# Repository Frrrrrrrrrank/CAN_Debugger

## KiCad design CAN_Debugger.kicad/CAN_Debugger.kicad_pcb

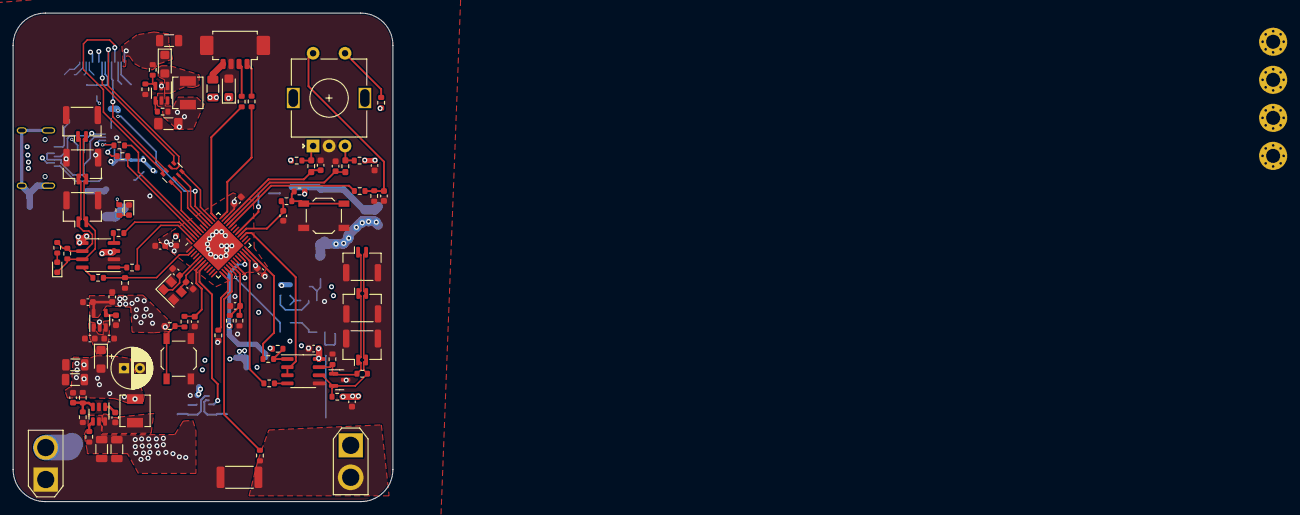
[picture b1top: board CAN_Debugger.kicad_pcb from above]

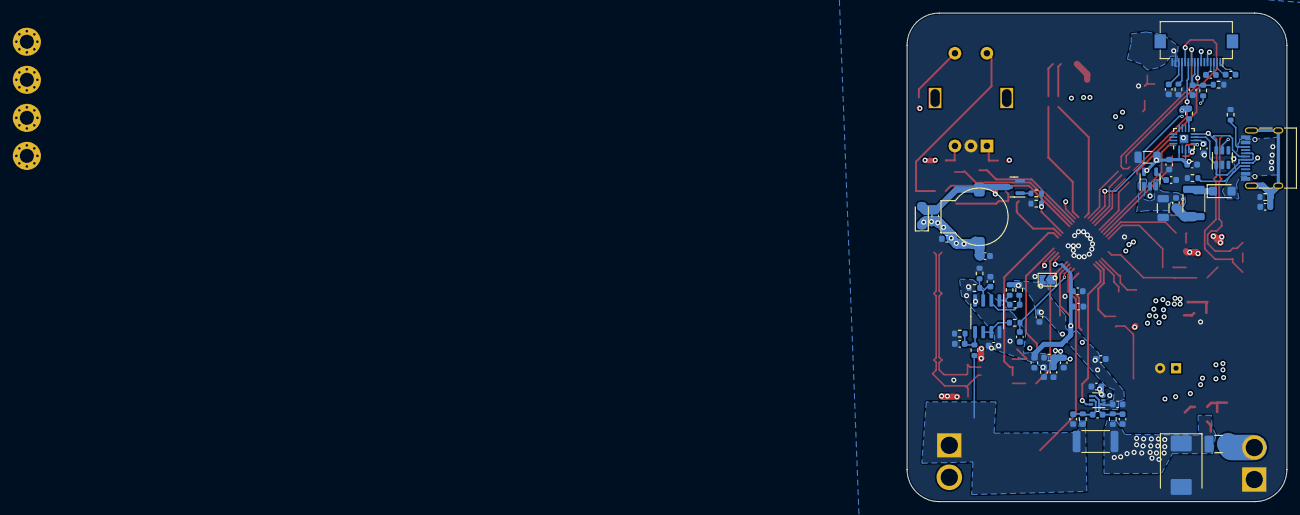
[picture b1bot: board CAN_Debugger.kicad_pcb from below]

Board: 4 copper layers, 59.4 x 76.4 mm, 169 parts (68 on the bottom side), 102 nets.

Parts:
BZ1: Buzzer; MLT-9032
C1, C2, C6, C7, C37, C45: 10uF; C_1206_3216Metric
C3: 47uF; CP_Radial_D6.3mm_P2.50mm
C4, C9, C12, C25, C26, C27, C28, C30, C31, C33, C34, C35, C38, C39, C40, C41, C42, C46, C49, C50, C57, C58, C59, C70, C76, C88, C104, C105: 100n; C_0603_1608Metric
C5, C8, C14, C23: 20p; C_0603_1608Metric
C10, C13, C22, C24, C29, C80: 10u; C_0603_1608Metric
C11: 10n; C_0603_1608Metric
C15, C16: 1uf; C_0603_1608Metric
C17: 2.2uf; C_0603_1608Metric
C20, C21, C36: 100nF; C_0603_1608Metric
C32, C47, C52, C53, C54: C; C_0603_1608Metric
C43, C44: 10nF; C_0603_1608Metric
C48: 22u; C_1206_3216Metric
C51: 22u; C_1206_3216Metric_Pad1.33x1.80mm_HandSolder
D1: SMCJ28A; D_SMC
D3, D5, D6, D10: D_Schottky; D_SMF
D4, D9: LED; LED_0603_1608Metric
D7: SMF3.3A; D_SMF
D8: SM712; SOT-23
F1: Fuse; Fuse_1210_3225Metric_Pad1.42x2.65mm_HandSolder
F2: Polyfuse; Fuse_1206_3216Metric
F4: Fuse; Fuse_1812_4532Metric
FB1: 120R@100MHz; L_0603_1608Metric
H1, H2, H3, H4: MountingHole_Pad; MountingHole_2.2mm_M2_Pad_Via
J1: Conn_01x02; AMASS_XT30U-M_1x02_P5.0mm_Vertical
J2: Conn_01x04_MountingPin; Molex_PicoBlade_53261-0471_1x04-1MP_P1.25mm_Horizontal
J3: Conn_01x02; AMASS_XT30U-F_1x02_P5.0mm_Vertical
J4: Conn_01x16_Socket; Hirose_FH12-16S-0.5SH_1x16-1MP_P0.50mm_Horizontal
J5: USB_C_Receptacle_USB2.0; USB_C_Receptacle_HRO_TYPE-C-31-M-12
J6: RS-485; JST_GH_BM02B-GHS-TBT_1x02-1MP_P1.25mm_Vertical
J7, J8, J9: CAN; JST_GH_BM02B-GHS-TBT_1x02-1MP_P1.25mm_Vertical
J15, J16: RS-485; JST_GH_SM02B-GHS-TB_1x02-1MP_P1.25mm_Horizontal
JP1: SolderJumper_2_Open; SolderJumper-2_P1.3mm_Open_TrianglePad1.0x1.5mm
L1: L; L_Sunlord_MWSA0402S
L2: 4.7u; L_Sunlord_MWSA0402S
L3: L_Ferrite; L_0603_1608Metric
Q1: AO3400A; SOT-23
R1, R3, R10, R19, R23, R28, R38, R39, R40, R42, R50: 10k; R_0603_1608Metric
R2: 53.6k; R_0603_1608Metric
R4, R44: R; R_2512_6332Metric
R5: 330R; R_0603_1608Metric
R6, R31: 10k; R_0603_1608Metric_Pad0.98x0.95mm_HandSolder
R7, R8, R11, R20, R63: 33r; R_0603_1608Metric
R9, R12, R13, R57: 120r; R_0603_1608Metric
R14, R15, R45, R51: R; R_0603_1608Metric
R16, R17, R21: 100k 25ppm; R_0603_1608Metric
R18, R22, R27: 330; R_0603_1608Metric
R24, R62: 1k; R_0603_1608Metric
R25: 10k 25ppm; R_0603_1608Metric
R29: 120R; R_0603_1608Metric
R30, R36: 10K; R_0603_1608Metric
R32, R33: 33R; R_0603_1608Metric
R34, R35: 5.1k; R_0603_1608Metric
R37: 1M; R_0603_1608Metric
R41, R48, R52: 100k; R_0603_1608Metric
R53, R56, R58: 4.7k; R_0603_1608Metric
R54, R55: 100; R_0603_1608Metric
R59, R60: 100r 25ppm; R_0603_1608Metric
R61: 19k; R_0603_1608Metric
RN1: R_Pack04; R_Array_Convex_4x0603
SW1, SW3: SW_Push; SW_SPST_TL3342
SW4: RotaryEncoder_Switch; RotaryEncoder_Alps_EC11E-Switch_Vertical_H20mm
U1: SN75176AD; SOIC-8_3.9x4.9mm_P1.27mm
U2: RY8411; SOT-23-6
U3, U10: RS3236; SOT-23-5
U5: SIT1042T/3; SOIC-8_3.9x4.9mm_P1.27mm
U6: IP4220CZ6; SOT-23-6
U7: INA186; SOT-363_SC-70-6
U8: STM32G431CBUx; QFN-48-1EP_7x7mm_P0.5mm_EP5.6x5.6mm
U9: CH343P; TQFN-16-1EP_3x3mm_P0.5mm_EP1.23x1.23mm
U13: MT3608; SOT-23-6
U14: GS8332-SR; SOIC-8_3.9x4.9mm_P1.27mm
Y1: 25MHz; Crystal_SMD_3225-4Pin_3.2x2.5mm

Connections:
24v_motor: J3.1, R4.2, R21.2, R60.1
+3.3V: C12.1, C13.1, C25.1, C26.1, C27.1, C28.1, C32.1, C41.1, C42.1, C52.1, D7.1 (A1), F2.1, J4.7, L3.1, R19.1, R23.1, R38.1, R39.2, R40.1, R53.1, U3.5 (OUT), U5.5 (VIO), U7.3 (V+), U8.1 (VBAT), U8.23 (VDD), U8.35 (VDD), U8.48 (VDD)
+3.3VA: C29.1, C30.1, C53.1, C54.1, C70.1, L3.2, R16.2, R48.1, U8.21 (VDDA), U14.8 (VDD)
+3.3V_USBTTL: C20.1, C21.1, C36.1, C45.1, U9.1 (VIO), U9.3 (VDD5), U9.6 (V3), U10.5 (OUT)
+5V: BZ1.2 (+), C1.1, C2.1, C3.1, C5.1, C22.2, C23.2, C24.2, C49.1, C50.1, C51.1, D3.2 (A), D5.1 (K), J4.5, L1.2, L2.1, R2.1, R50.1, R58.2, U1.8 (VCC), U5.3 (VCC), U13.5 (IN)
+24V: C6.1, C7.1, D1.1 (K), F1.1, R1.1, R4.1, R59.1, U2.5 (IN)
/1.65Vref: C40.1, C76.1, C80.1, JP1.2 (B), R20.1, R24.1, U7.1 (REF)
/VBUS_CONNECTOR: D6.2 (A), J5.A4 (VBUS), J5.A9 (VBUS), J5.B4 (VBUS), J5.B9 (VBUS)
A+: D8.2 (A2), J6.2, J15.2, J16.2, R57.2, R58.1, U1.6 (A)
A_I: U7.6, U8.8 (PA0)
B-: D8.1 (A1), J6.1, J15.1, J16.1, R56.2, R57.1, U1.7 (B)
BUZZER: R10.2, R11.1, U8.29 (PC6)
C1N: C16.2, J4.4
C1P: C16.1, J4.3
C2N: C15.2, J4.2
C2P: C15.1, J4.1
CANH: D9.1 (K), J7.2, J8.2, J9.2, R9.2, U5.7 (CANH)
CANL: J7.1, J8.1, J9.1, R9.1, R15.1, U5.6 (CANL)
CAN_RX: R8.1, U8.46 (PB8)
CAN_STB: R29.1, R30.1, U8.2 (PC13)
CAN_TX: R7.1, U8.47 (PB9)
CS: J4.8, RN1.5 (R4.2)
D/C: J4.10, RN1.6 (R3.2)
Encoder_button: R42.1, U8.32 (PA10)
GND: C1.2, C2.2, C3.2, C6.2, C7.2, C8.2, C9.2, C10.2, C11.2, C12.2, C13.2, C14.2, C17.2, C20.2, C21.2, C22.1, C24.1, C25.2, C26.2, C27.2, C28.2, C29.2, C30.2, C31.1, C32.2, C33.1, C35.1, C36.2, C37.2, C38.1, C39.2, C40.2, C41.2, C42.2, C43.1, C44.2, C45.2, C46.2, C47.2, C48.2, C49.2, C50.2, C51.2, C52.2, C53.2, C54.2, C57.2, C59.2, C70.2, C76.2, C80.2, C88.1, C104.1, C105.2, D1.2 (A), D4.1 (K), D7.2 (A2), D8.3 (common), J1.1, J2.3, J2.MP (MountPin), J4.16, J5.A1 (GND), J5.A12 (GND), J5.B1 (GND), J5.B12 (GND), J6.MP (MountPin), J7.MP (MountPin), J8.MP (MountPin), J9.MP (MountPin), J15.MP (MountPin), J16.MP (MountPin), Q1.2 (S), R3.2, R10.1, R14.2, R17.1, R25.1, R28.2, R30.2, R34.1, R35.1, R37.1, R41.2, R44.1, R51.2, R52.2, R56.1, R62.2, SW1.2, SW3.2, SW4.C, U1.5 (GND), U2.2 (GND), U3.2 (GND), U5.2 (GND), U6.2 (VN), U7.2 (GND), U8.49 (VSS), U9.2 (GND), U9.17 (GND), U10.2 (GND), U13.2 (GND), U14.4 (VSS), Y1.2, Y1.4
IREF: J4.13, R14.1
NRST: C31.2, R18.2, U8.7 (PG10)
unnamed: BZ1.1 (-), C23.1, D5.2 (A), Q1.3 (D)
unnamed: C46.1, R41.1, R42.2, SW4.S2
unnamed: C57.1, R16.1, R17.2, U14.3 (+)
unnamed: C58.2, R24.2, U14.2 (-)
unnamed: C59.1, R21.1, R25.2, U14.5 (+)
unnamed: C9.1, C10.1, D3.1 (K), U3.1 (IN), U3.3 (EN)
unnamed: D4.2 (A), R36.2
unnamed: D6.1 (K), F4.2
unnamed: D9.2 (A), R15.2
unnamed: D10.2 (A), L2.2, U13.1 (SW)
unnamed: F4.1, FB1.2
unnamed: F1.2, J1.2
unnamed: J2.1, R13.2
unnamed: J2.2, R12.2
unnamed: F2.2, J2.4
unnamed: J5.A5 (CC1), R34.2
unnamed: J5.B5 (CC2), R35.2
unnamed: C43.2, J5.S1 (SHIELD), R37.2
unnamed: Q1.1 (G), R11.2
unnamed: R18.1, R19.2, SW1.1
unnamed: R22.1, R23.2, SW3.1
unnamed: R31.2, R38.2, SW4.B
unnamed: R6.2, R39.1, SW4.A
unnamed: R40.2, SW4.S1
unnamed: R54.1, U1.4 (D)
unnamed: R53.2, R55.2, U1.1 (R)
unnamed: C4.1, U2.1 (BS)
unnamed: R1.2, U2.4 (EN)
unnamed: C5.2, R2.2, R3.1, U2.3 (FB)
unnamed: C4.2, L1.1, U2.6 (LX)
unnamed: C11.1, U3.4 (BP/FB)
unnamed: R8.2, U5.4 (RXD)
unnamed: R29.2, U5.8 (STB)
unnamed: R7.2, U5.1 (TXD)
unnamed: C34.1, C104.2, R59.2, U7.4 (+)
unnamed: C34.2, C105.1, R60.2, U7.5 (-)
unnamed: R32.2, U9.5 (RXD)
unnamed: R33.1, U9.4 (TXD)
unnamed: R5.1, U9.9 (VBUS)
unnamed: C44.1, U10.4 (BP)
unnamed: R50.2, U13.4 (EN)
unnamed: R61.2, R62.1, U13.3 (FB)
unnamed: C58.1, R20.2, U14.1 (OUTA)
unnamed: R63.1, U14.6 (-), U14.7 (OUTB)
PA5: R51.1, U8.13 (PA5)
PA7: R45.1, U8.15 (PA7)
PA11: C39.1, R31.1, U8.33 (PA11)
PA12: C38.2, R6.1, U8.34 (PA12)
PA15: RN1.4 (R4.1), U8.38 (PA15)
PB0: C47.1, R48.2, R52.1, U8.17 (PB0)
PB1: JP1.1 (A), U8.18 (PB1)
PB6: R32.1, U8.44 (PB6)
PB7: R33.2, U8.45 (PB7)
PB10: R54.2, U8.22 (PB10)
PB11: R55.1, U8.24 (PB11)
PB14: U1.2 (~RE), U1.3 (DE), U8.27 (PB14)
PB15: C33.2, R22.2, U8.28 (PB15)
PC4: C88.2, R63.2, U8.16 (PC4)
PC10: R27.1, U8.39 (PC10)
PC11: RN1.3 (R3.1), U8.40 (PC11)
RCC_OSC_IN: C14.1, U8.5 (PF0), Y1.1
RCC_OSC_OUT: C8.1, U8.6 (PF1), Y1.3
RES: C35.2, J4.9, R27.2, R28.1
SCLK: J4.11, RN1.7 (R2.2)
SDIN: J4.12, RN1.8 (R1.2)
SPI1_MOSI: RN1.1 (R1.1), U8.43 (PB5)
SPI1_SCK: RN1.2 (R2.1), U8.41 (PB3)
SYS_JTCK-SWDCLK: R12.1, U8.37 (PA14)
SYS_JTMS-SWDIO: R13.1, U8.36 (PA13)
USB_UART_DM: J5.A7 (D-), J5.B7 (D-), U6.6 (IO4), U9.8 (VD-)
USB_UART_DP: J5.A6 (D+), J5.B6 (D+), U6.1 (IO1), U9.7 (VD+)
VBUS_USBTTL: C37.1, FB1.1, R5.2, R36.1, U6.5 (VP), U10.1 (IN), U10.3 (EN)
VCC: C48.1, D10.1 (K), J4.15, R61.1
VCOMH: C17.1, J4.14
iA+: J3.2, R44.2, R45.2

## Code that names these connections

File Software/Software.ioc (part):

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Mcu.Name=STM32G431C(6-8-B)Ux
Mcu.Package=UFQFPN48
Mcu.UserName=STM32G431CBUx
PA0.GPIOParameters=GPIO_Label
PA0.GPIO_Label=I_AMPLIFIED_SENSE
PA0.Mode=IN1-Single-Ended
PA0.Signal=ADC2_IN1
PA10.Signal=GPIO_Input
PA11.Signal=S_TIM4_CH1
PA12.Signal=S_TIM4_CH2
PA13.Mode=Serial_Wire
PA13.Signal=SYS_JTMS-SWDIO
PA14.Mode=Serial_Wire
PA14.Signal=SYS_JTCK-SWCLK
PA15.Mode=NSS_Signal_Hard_Output
PA15.Signal=SPI1_NSS
PA5.Mode=PGA Internally connected_IO0_BIAS
PA5.Signal=OPAMP2_VINM0
PA7.Mode=PGA Internally connected_IO0_BIAS
PA7.Signal=OPAMP2_VINP
PB10.Mode=Asynchronous
PB10.Signal=USART3_TX
PB11.Mode=Asynchronous
PB11.Signal=USART3_RX
PB14.Mode=Hardware Flow Control (RS485)
PB14.Signal=USART3_DE
PB15.GPIOParameters=GPIO_Label
PB15.GPIO_Label=BTN1
PB15.Signal=GPIO_Input
PB3.Mode=TX_Only_Simplex_Unidirect_Master
PB3.Signal=SPI1_SCK
PB5.Mode=TX_Only_Simplex_Unidirect_Master
PB5.Signal=SPI1_MOSI
PB6.Mode=Asynchronous
PB6.Signal=USART1_TX
PB7.Mode=Asynchronous
PB7.Signal=USART1_RX
PB8-BOOT0.Mode=FDCAN_Activate
PB8-BOOT0.Signal=FDCAN1_RX
PB9.Mode=FDCAN_Activate
PB9.Signal=FDCAN1_TX
PC10.GPIOParameters=GPIO_Label
PC10.GPIO_Label=OLED_RST
PC10.Signal=GPIO_Output
PC11.GPIOParameters=GPIO_Label
PC11.GPIO_Label=OLED_DC
PC11.Signal=GPIO_Output
PC13.GPIOParameters=GPIO_Label
PC13.GPIO_Label=CAN_STB
PC13.Signal=GPIO_Output
PC4.GPIOParameters=GPIO_Label
PC4.GPIO_Label=V_BUFFERED_SENSE
PC4.Mode=IN5-Single-Ended
PC4.Signal=ADC2_IN5
PC6.Signal=S_TIM8_CH1
PF0-OSC_IN.Mode=HSE-External-Oscillator
PF0-OSC_IN.Signal=RCC_OSC_IN
PF1-OSC_OUT.Mode=HSE-External-Oscillator
PF1-OSC_OUT.Signal=RCC_OSC_OUT
RCC.HSE_VALUE=25000000
RCC.SYSCLKFreq_VALUE=170000000
RCC.SYSCLKSource=RCC_SYSCLKSOURCE_PLLCLK
board=custom

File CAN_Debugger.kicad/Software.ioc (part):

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Mcu.Name=STM32G431C(6-8-B)Ux
Mcu.Package=UFQFPN48
Mcu.UserName=STM32G431CBUx
PA1.GPIOParameters=GPIO_Label
PA1.GPIO_Label=CAN_H_OPAMP_INPUT
PA1.Mode=Follower_Internally_Connected
PA1.Signal=OPAMP1_VINP
PA10.Signal=GPIO_Input
PA11.Signal=S_TIM4_CH1
PA12.Signal=S_TIM4_CH2
PA13.Mode=Serial_Wire
PA13.Signal=SYS_JTMS-SWDIO
PA14.Mode=Serial_Wire
PA14.Signal=SYS_JTCK-SWCLK
PA15.Mode=NSS_Signal_Hard_Output
PA15.Signal=SPI1_NSS
PA3.GPIOParameters=GPIO_Label
PA3.GPIO_Label=CAN_L_OPAMP_INPUT
PA3.Mode=Switching On Non Inverting Inputs Using Different Pins
PA3.Signal=OPAMP1_VINP_SEC
PA4.GPIOParameters=GPIO_Label
PA4.GPIO_Label=I_SHUNT_AMPLIFIED_SENSE
PA4.Mode=IN17-Single-Ended
PA4.Signal=ADC2_IN17
PA5.Mode=PGA Connected
PA5.Signal=OPAMP2_VINM0
PA6.Mode=PGA Connected
PA6.Signal=OPAMP2_VOUT
PA7.Mode=PGA Connected
PA7.Signal=OPAMP2_VINP
PB0.Mode=Standalone
PB0.Signal=OPAMP3_VINP
PB1.Mode=Standalone
PB1.Signal=OPAMP3_VOUT
PB10.Mode=Asynchronous
PB10.Signal=USART3_TX
PB11.Mode=Asynchronous
PB11.Signal=USART3_RX
PB14.Mode=Hardware Flow Control (RS485)
PB14.Signal=USART3_DE
PB2.Mode=Standalone
PB2.Signal=OPAMP3_VINM
PB3.Mode=TX_Only_Simplex_Unidirect_Master
PB3.Signal=SPI1_SCK
PB5.Mode=TX_Only_Simplex_Unidirect_Master
PB5.Signal=SPI1_MOSI
PB6.Mode=Asynchronous
PB6.Signal=USART1_TX
PB7.Mode=Asynchronous
PB7.Signal=USART1_RX
PB8-BOOT0.Mode=FDCAN_Activate
PB8-BOOT0.Signal=FDCAN1_RX
PB9.Mode=FDCAN_Activate
PB9.Signal=FDCAN1_TX
PC10.GPIOParameters=GPIO_Label
PC10.GPIO_Label=OLED_RST
PC10.Signal=GPIO_Output
PC11.GPIOParameters=GPIO_Label
PC11.GPIO_Label=OLED_DC
PC11.Signal=GPIO_Output
PC13.GPIOParameters=GPIO_Label
PC13.GPIO_Label=CAN_STB
PC13.Signal=GPIO_Output
PC4.GPIOParameters=GPIO_Label
PC4.GPIO_Label=V_SENSE
PC4.Mode=IN5-Single-Ended
PC4.Signal=ADC2_IN5
PF0-OSC_IN.Mode=HSE-External-Oscillator
PF0-OSC_IN.Signal=RCC_OSC_IN
PF1-OSC_OUT.Mode=HSE-External-Oscillator
PF1-OSC_OUT.Signal=RCC_OSC_OUT
RCC.HSE_VALUE=25000000
RCC.SYSCLKFreq_VALUE=170000000
RCC.SYSCLKSource=RCC_SYSCLKSOURCE_PLLCLK
board=custom

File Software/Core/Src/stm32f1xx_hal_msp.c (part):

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
    __HAL_RCC_GPIOA_CLK_ENABLE();
    /**ADC1 GPIO Configuration
    PA0-WKUP     ------> ADC1_IN0
    PA2     ------> ADC1_IN2
    */
    GPIO_InitStruct.Pin = GPIO_PIN_0|GPIO_PIN_2;
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    __HAL_RCC_ADC1_CLK_DISABLE();

    /**ADC1 GPIO Configuration
    PA0-WKUP     ------> ADC1_IN0
    PA2     ------> ADC1_IN2
    */
    HAL_GPIO_DeInit(GPIOA, GPIO_PIN_0|GPIO_PIN_2);
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
    __HAL_RCC_GPIOB_CLK_ENABLE();
    /**CAN GPIO Configuration
    PB8     ------> CAN_RX
    PB9     ------> CAN_TX
    */
    GPIO_InitStruct.Pin = GPIO_PIN_8;
    GPIO_InitStruct.Mode = GPIO_MODE_INPUT;
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    __HAL_RCC_CAN1_CLK_DISABLE();

    /**CAN GPIO Configuration
    PB8     ------> CAN_RX
    PB9     ------> CAN_TX
    */
    HAL_GPIO_DeInit(GPIOB, GPIO_PIN_8|GPIO_PIN_9);

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
    __HAL_RCC_GPIOA_CLK_ENABLE();
    /**SPI1 GPIO Configuration
    PA5     ------> SPI1_SCK
    PA6     ------> SPI1_MISO
    PA7     ------> SPI1_MOSI
    */
    GPIO_InitStruct.Pin = GPIO_PIN_5|GPIO_PIN_7;
    GPIO_InitStruct.Mode = GPIO_MODE_AF_PP;
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    __HAL_RCC_SPI1_CLK_DISABLE();

    /**SPI1 GPIO Configuration
    PA5     ------> SPI1_SCK
    PA6     ------> SPI1_MISO
    PA7     ------> SPI1_MOSI
    */
    HAL_GPIO_DeInit(GPIOA, GPIO_PIN_5|GPIO_PIN_6|GPIO_PIN_7);

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
    __HAL_RCC_GPIOB_CLK_ENABLE();
    /**USART1 GPIO Configuration
    PB6     ------> USART1_TX
    PB7     ------> USART1_RX
    */
    GPIO_InitStruct.Pin = GPIO_PIN_6;
    GPIO_InitStruct.Mode = GPIO_MODE_AF_PP;
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    __HAL_RCC_USART1_CLK_DISABLE();

    /**USART1 GPIO Configuration
    PB6     ------> USART1_TX
    PB7     ------> USART1_RX
    */
    HAL_GPIO_DeInit(GPIOB, GPIO_PIN_6|GPIO_PIN_7);

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
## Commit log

2023-09-01 init ioc
2023-09-02 Add files via upload
    update sch
2023-09-04 Kicad Schematic done
2023-09-06 Changing schematic; Change cubemx ioc to G431
2023-09-06 Edit ioc
2023-09-08 update sch
2023-09-13 schematic
2023-09-21 update sche
2023-10-03 update schematic
2023-10-07 Add Hardware Core; Add Handsolder QFN48 Footprint; Changes in schematic texts
2023-10-07 Add ignore backup folder
2023-10-15 Update PCB layout
2023-10-26 Generated Code from CubeMX and CLion
2023-10-26 Update gitignore
2023-11-02 Add C++ Tasks.cpp; Still some bugs, cannot compile cpp
2023-11-04 1. Able to compile by cmake; Makefile still cannot. 2. Able to beep 3. Able to read ADC of input voltage (But with big noise) -- Need VREF changes 4. Needs Boot0 changes
2023-11-05 1. Use External VRef: shorted VREF and VDDA 2. Read Amplified Current Value
2023-11-08 1. Update Makefile 2. Able to read current and voltage 3. Internal Opamp for current sense

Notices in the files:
Software/Core/Src/stm32f1xx_hal_msp.c:
Copyright (c) 2023 STMicroelectronics.
All rights reserved.
This software is licensed under terms that can be found in the LICENSE file
